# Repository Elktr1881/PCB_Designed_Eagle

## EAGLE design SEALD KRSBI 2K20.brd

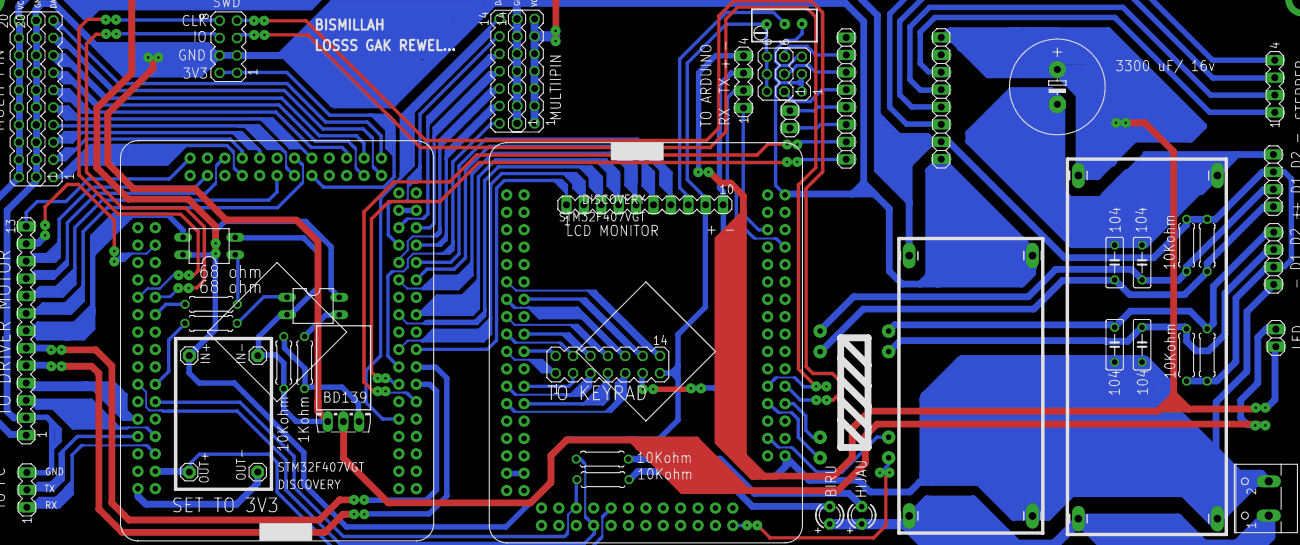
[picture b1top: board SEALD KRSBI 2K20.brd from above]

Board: 2 copper layers, 55 parts (0 on the bottom side), 7 nets.

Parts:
E$1, E$42: DIL04
E$2, E$20, E$21, E$43, E$44, E$45, E$49, E$50, E$51, E$52: 0207/7
E$3: MA03-1
E$5, E$6, E$38, E$40: C050-025X075
E$7: MA04-2
E$8: MA10-1
E$9: RTRIMT93YA
E$10, E$11: MA10-2
E$12, E$13, E$23, E$24, E$25, E$26, E$27, E$28: 1X01_LONGPAD
E$14: TO126AV
E$15, E$22: 1X04
E$16: MA13-1
E$17: E5-13
E$18, E$19: LED3MM
E$29: W237-102
E$30, E$31: 1X08
E$32, E$33: MA03-2
E$34, E$37: 1X02
E$35, E$36: MA04-1
E$46, E$47, E$48: MA07-2
IN+: 1X01
IN-: 1X01
OUT+: 1X01
OUT-: 1X01
U$1, U$2: STM32F407(BOARD); STM32F407VGT

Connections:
unnamed: U$1.PB10, U$1.PB11
unnamed: U$1.PD8, U$1.PD9
unnamed: U$1.PC6, U$1.PC7
unnamed: U$1.PA9, U$1.PA10
unnamed: U$1.PC10, U$1.PC11
unnamed: U$1.PD5, U$1.PD6
unnamed: U$1.PB6, U$1.PB7

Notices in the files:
parts and their libraries:
SparkFun-Connectors: Licensing: Creative Commons ShareAlike 4.0 International - https://creativecommons.org/licenses/by-sa/4.0
